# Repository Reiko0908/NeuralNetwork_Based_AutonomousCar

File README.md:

# NeuralNetwork_Based_AutonomousCar

## Project Overview
This project focuses on developing an autonomous car system powered by neural networks (NN). Inspired by the design architecture of micromouse, the car is designed to navigate autonomously using deep learning techniques. The project leverages deep learning and neural network models to enable the autonomous functionalities of the car. The neural network processes real-world sensor data to make real-time decisions for the car's navigation. The project timeline is divided into several stages:
1. **Concept Development**: Initial phase where the concept was developed.
2. **Gamepad PCB Design**: Creation of the gamepad hardware to control the car.
3. **Autonomous Car Design**: Currently in progress, focusing on the car's hardware and software integration.
4. **Neural Network Training**: Future phase where the model will be trained.
5. **Documentation**: Final phase to document the project.

## Software Architecture
- **Data Collection**: Using the gamepad (now replaced by computer control) to navigate the car in a physical map with walls. The sensors collect data and transmit it to the ESP32-S3 on the computer.
- **Machine Learning Training**: Utilizing Python and TensorFlow to train the neural network model.
- **Deployment**: Importing the trained model configurations to the car for autonomous navigation.

## Hardware

### Car Hardware
- **ESP32-S3 Super Mini**: Main microcontroller used in the car.
- **GY87 9-DOF IMU**: Inertial measurement unit for orientation and motion sensing.
- **5 VL53L0X Sensors**: Distance measurement sensors for mapping the environment.
- **L293DD Motor Driver**: Controls the motors of the car.
- **GA12 N20 Motor**: Motor with a step-up gearbox of 56:16 for movement.
- **2S Lipo Battery**

### Gamepad Hardware
- **Joysticks**
- **MPU6050 6-DOF IMU**
- **ESP32-S3 N16R8**
- **ST7789 LCD TFT SPI Screen**
- **IP5306 for Power Management**
- **Low Profile Switches**
- **Single-cell 18650 Battery**
- **Additional Buttons and Pin Headers**

## Machine Learning Training Procedure
1. **Collecting Data**: Create a physical map with walls and use the gamepad (now our computer) to control the car. The 5 VL53L0X sensors onboard will collect map data, transmit them to the ESP on the computer.
2. **Training the Model**: Use Python with TensorFlow library to train the neural network model.
3. **Deployment**: Import the trained model configurations to the car and let it navigate autonomously.

### Milestone Pictures
- **Micromouse Design Inspiration**

- **Gamepad PCB**

## Additional Information
The gamepad PCB encountered a hardware issue that cannot be fixed in time. As a workaround, we will use an external ESP32-S3 connected to the computer to control the car via BLE. We will continue to develop and improve the project.

---

*Author: pacman314159*

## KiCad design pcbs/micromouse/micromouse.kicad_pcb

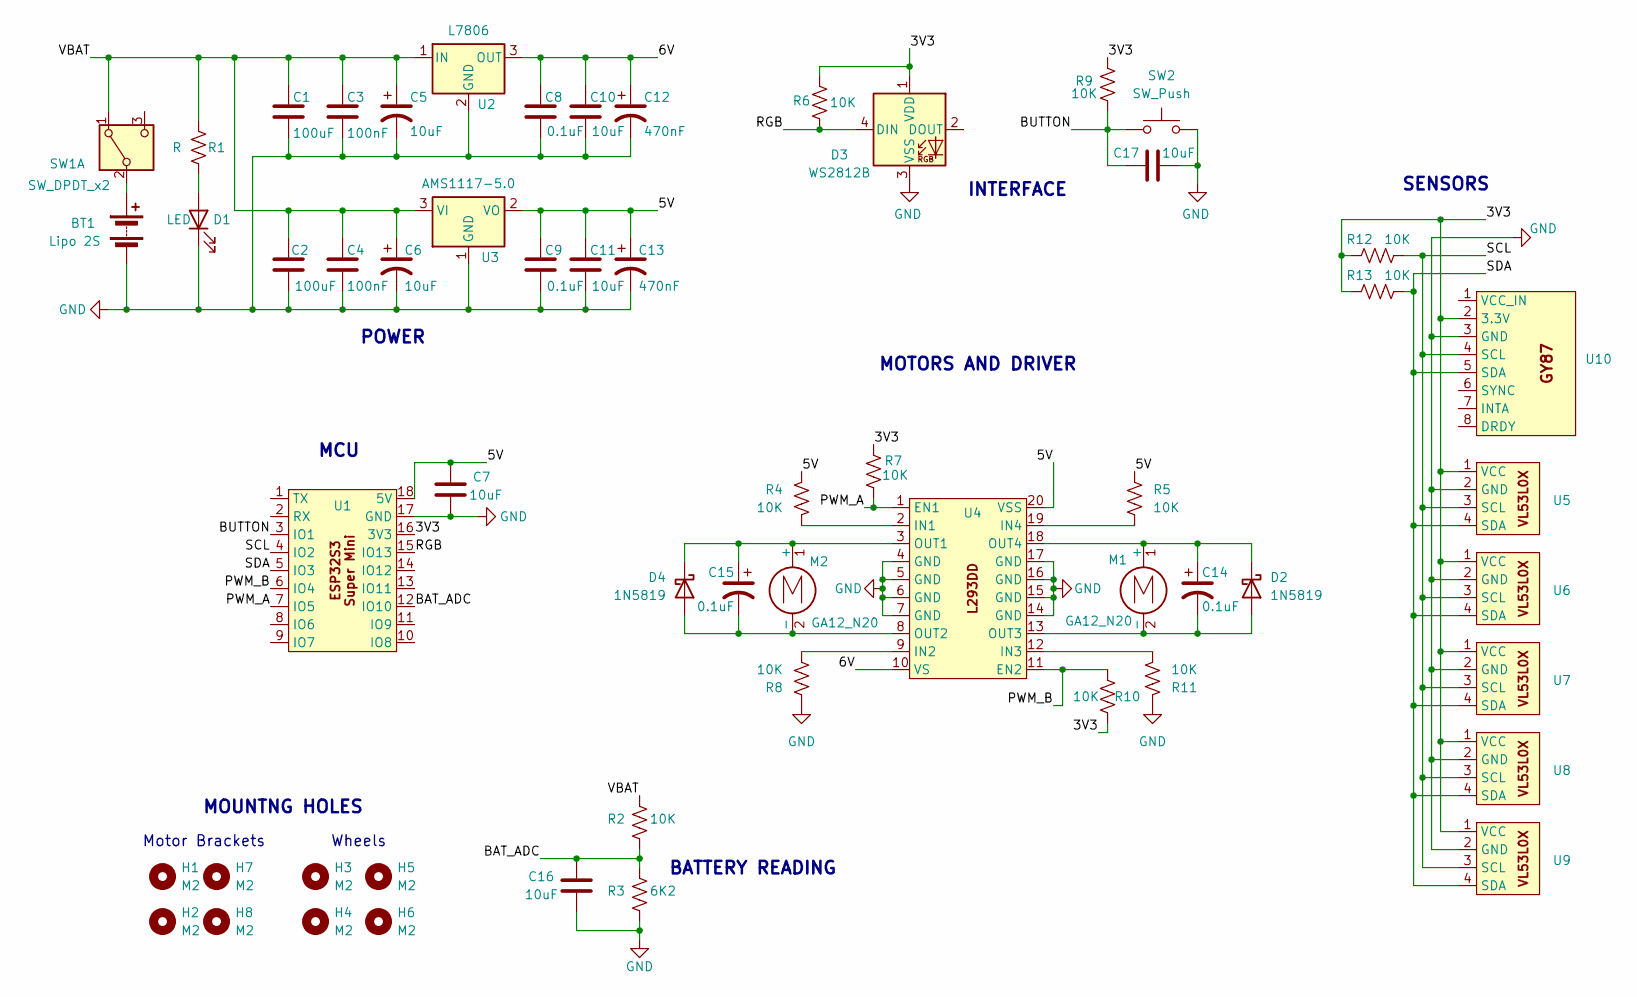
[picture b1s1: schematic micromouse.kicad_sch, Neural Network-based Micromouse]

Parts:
BT1: Lipo 2S; 2P_male
C1, C2: 100uF; C_0805_2012Metric_Pad1.18x1.45mm_HandSolder
C3, C4: 100nF; C_0805_2012Metric_Pad1.18x1.45mm_HandSolder
C5, C6: 10uF; CP_Radial_D5.0mm_P2.00mm
C7, C10, C11, C16, C17: 10uF; C_0805_2012Metric_Pad1.18x1.45mm_HandSolder
C8, C9: 0.1uF; C_0805_2012Metric_Pad1.18x1.45mm_HandSolder
C12, C13: 470nF; CP_Radial_D5.0mm_P2.00mm
C14, C15: 0.1uF; CP_Radial_D5.0mm_P2.00mm
D1: LED; LED_0805_2012Metric_Pad1.15x1.40mm_HandSolder
D2, D4: 1N5819; D_SOD-323F
D3: WS2812B; LED_WS2812B_PLCC4_5.0x5.0mm_P3.2mm
H1, H2, H3, H4, H5, H6, H7, H8: M2; MountingHole_2.2mm_M2
M1, M2: GA12_N20; 2P_male
R1: R; R_0805_2012Metric_Pad1.20x1.40mm_HandSolder
R2, R4, R5, R6, R7, R8, R9, R10, R11, R12, R13: 10K; R_0805_2012Metric_Pad1.20x1.40mm_HandSolder
R3: 6K2; R_0805_2012Metric_Pad1.20x1.40mm_HandSolder
SW1: SW_DPDT_x2; SW_SS12D07VG4
SW2: SW_Push; SW_SPST_CK_RS282G05A3
U1: esp32s3_super_mini
U2: L7806; TO-220-3_Vertical
U3: AMS1117-5.0; SOT-223-3_TabPin2
U4: SOP-20_7.5x12.8mm_P1.27mm
U5, U6, U7, U8, U9: VL53L0X_vertical
U10: GY87

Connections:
/3V3: D3.1 (VDD), R6.2, R7.2, R9.2, R10.2, R12.1, R13.1, U1.16 (3V3), U5.1 (VCC), U6.1 (VCC), U7.1 (VCC), U8.1 (VCC), U9.1 (VCC), U10.2 (3.3V)
/5V: C7.1, C9.1, C11.1, C13.1, R4.1, R5.1, U1.18 (5V), U3.2 (VO), U4.20 (VSS)
/6V: C8.1, C10.1, C12.1, U2.3 (OUT), U4.10 (VS)
/BAT_ADC: C16.1, R2.1, R3.2, U1.12 (IO10)
/BUTTON: C17.1, R9.1, SW2.1, U1.3 (IO1)
/PWM_A: R7.1, U1.7 (IO5), U4.1 (EN1)
/PWM_B: R10.1, U1.6 (IO4), U4.11 (EN2)
/RGB: D3.4 (DIN), R6.1, U1.15 (IO13)
/SCL: R12.2, U1.4 (IO2), U5.3 (SCL), U6.3 (SCL), U7.3 (SCL), U8.3 (SCL), U9.3 (SCL), U10.4 (SCL)
/SDA: R13.2, U1.5 (IO3), U5.4 (SDA), U6.4 (SDA), U7.4 (SDA), U8.4 (SDA), U9.4 (SDA), U10.5 (SDA)
/VBAT: C1.1, C2.1, C3.1, C4.1, C5.1, C6.1, R1.1, R2.2, SW1.1 (A), U2.1 (IN), U3.3 (VI)
GND: BT1.2 (-), C1.2, C2.2, C3.2, C4.2, C5.2, C6.2, C7.2, C8.2, C9.2, C10.2, C11.2, C12.2, C13.2, C16.2, C17.2, D1.1 (K), D3.3 (VSS), R3.1, R8.1, R11.1, SW2.2, U1.17 (GND), U2.2 (GND), U3.1 (GND), U4.4 (GND), U4.5 (GND), U4.6 (GND), U4.7 (GND), U4.14 (GND), U4.15 (GND), U4.16 (GND), U4.17 (GND), U5.2 (GND), U6.2 (GND), U7.2 (GND), U8.2 (GND), U9.2 (GND), U10.3 (GND)
unnamed: BT1.1 (+), SW1.2 (B)
unnamed: D1.2 (A), R1.2
unnamed: C14.2, D2.2 (A), M1.2 (-), U4.13 (OUT3)
unnamed: C14.1, D2.1 (K), M1.1 (+), U4.18 (OUT4)
unnamed: C15.2, D4.2 (A), M2.2 (-), U4.8 (OUT2)
unnamed: C15.1, D4.1 (K), M2.1 (+), U4.3 (OUT1)
unnamed: R4.2, U4.2 (IN1)
unnamed: R8.2, U4.9 (IN2)
unnamed: R11.2, U4.12 (IN3)
unnamed: R5.2, U4.19 (IN4)

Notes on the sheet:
MCU
MOUNTNG HOLES
POWER
BATTERY READING
Wheels
Motor Brackets
SENSORS
MOTORS AND DRIVER
INTERFACE

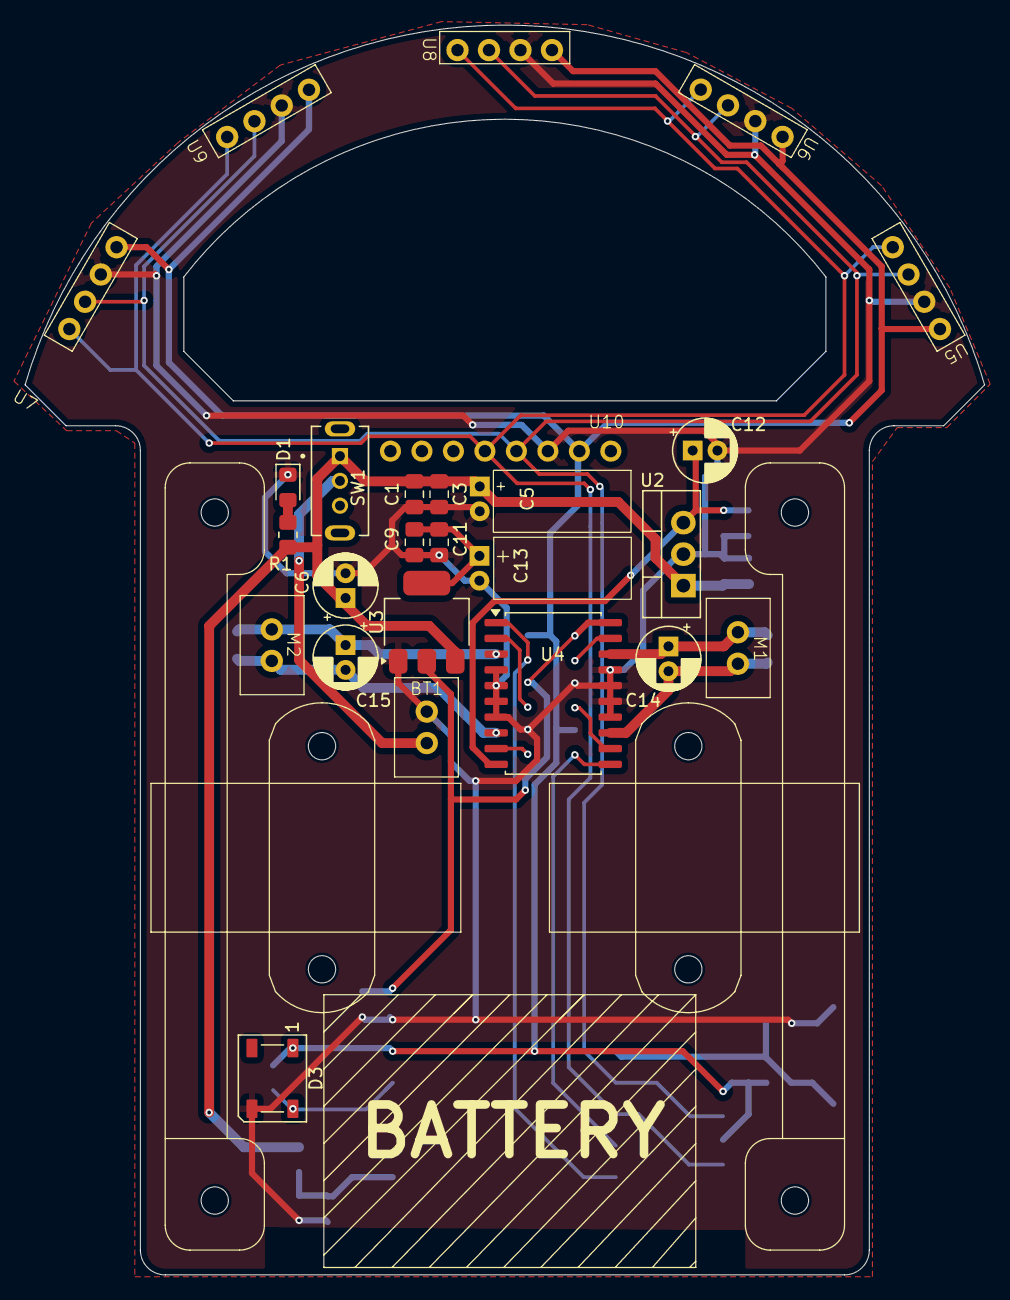
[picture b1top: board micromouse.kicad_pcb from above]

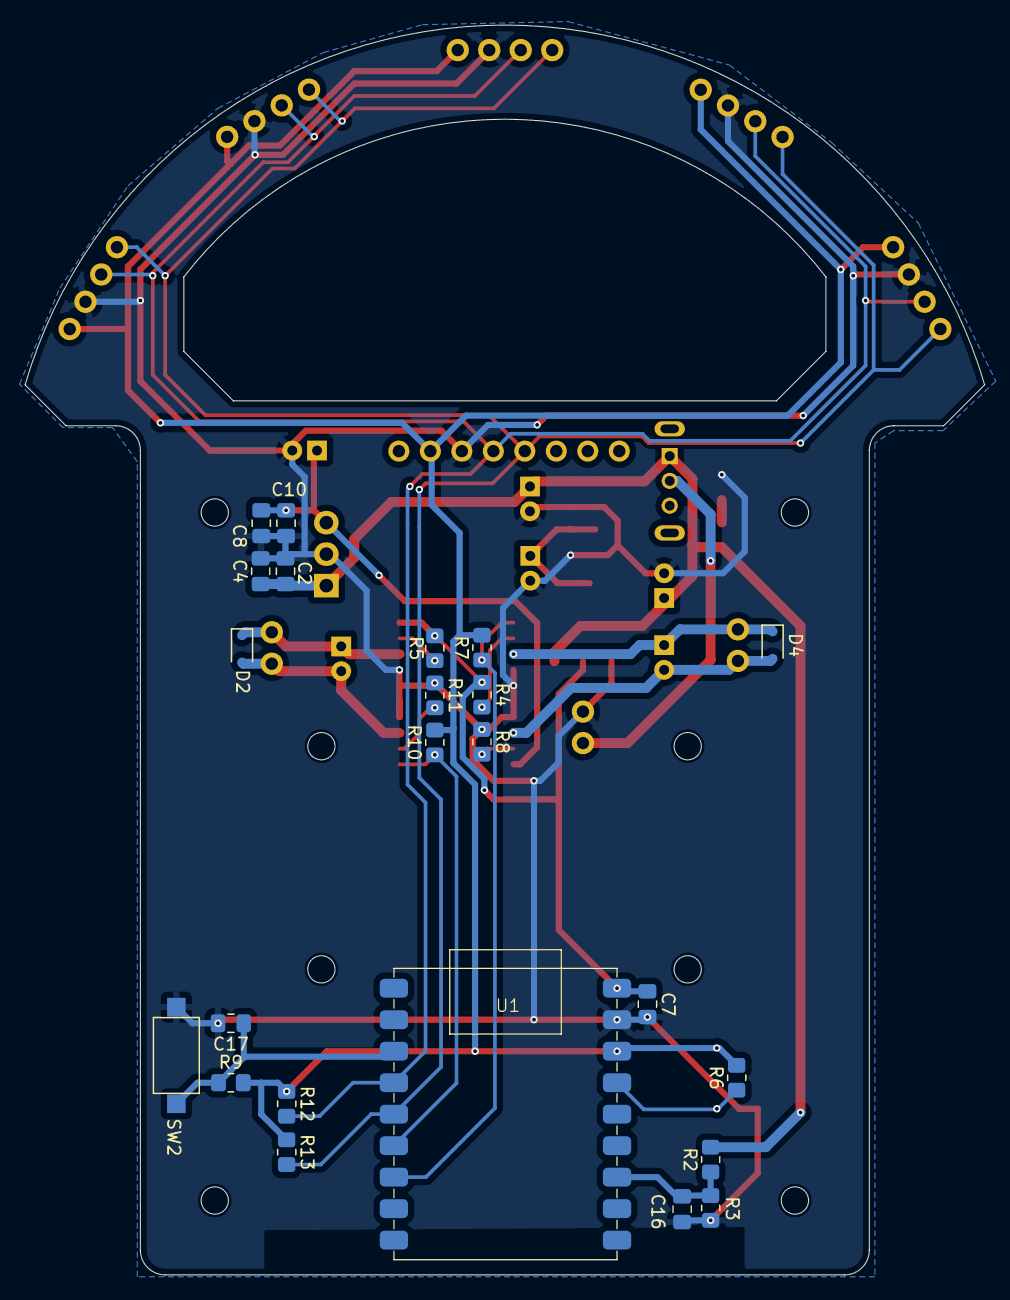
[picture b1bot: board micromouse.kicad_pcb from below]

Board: 2 copper layers, 77.4 x 100.8 mm, 57 parts (23 on the bottom side), 22 nets.

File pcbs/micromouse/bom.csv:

"Reference","Value","Datasheet","Footprint","Qty","DNP"
"BT1","Lipo 2S","~","XH_2p54:2P_male","1",""
"C1,C2","100uF","~","Capacitor_SMD:C_0805_2012Metric_Pad1.18x1.45mm_HandSolder","2",""
"C3,C4,C8,C9,C14,C15","0.1uF","~","-- mixed values --","6",""
"C5,C6,C7,C10,C11,C16,C17","10uF","~","-- mixed values --","7",""
"C12,C13","470nF","~","Capacitor_THT:CP_Radial_D5.0mm_P2.00mm","2",""
"D1","LED","~","LED_SMD:LED_0805_2012Metric_Pad1.15x1.40mm_HandSolder","1",""
"D2,D4","1N5819","http://www.vishay.com/docs/88525/1n5817.pdf","Diode_SMD:D_SOD-323F","2",""
"D3","WS2812B","https://cdn-shop.adafruit.com/datasheets/WS2812B.pdf","LED_SMD:LED_WS2812B_PLCC4_5.0x5.0mm_P3.2mm","1",""
"M1,M2","GA12_N20","~","XH_2p54:2P_male","2",""
"R1","R","~","Resistor_SMD:R_0805_2012Metric_Pad1.20x1.40mm_HandSolder","1",""
"R2,R4,R5,R6,R7,R8,R9,R10,R11,R12,R13","10K","~","Resistor_SMD:R_0805_2012Metric_Pad1.20x1.40mm_HandSolder","11",""
"R3","6K2","~","Resistor_SMD:R_0805_2012Metric_Pad1.20x1.40mm_HandSolder","1",""
"SW1","SW_DPDT_x2","~","SW_SS12D07VG4:SW_SS12D07VG4","1",""
"SW2","SW_Push","~","Button_Switch_SMD:SW_SPST_CK_RS282G05A3","1",""
"U1,U4,U5,U6,U7,U8,U9,U10","~","","-- mixed values --","8",""
"U2","L7806","http://www.st.com/content/ccc/resource/technical/document/da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","Package_TO_SOT_THT:TO-220-3_Vertical","1",""
"U3","AMS1117-5.0","http://www.advanced-monolithic.com/pdf/ds1117.pdf","Package_TO_SOT_SMD:SOT-223-3_TabPin2","1",""

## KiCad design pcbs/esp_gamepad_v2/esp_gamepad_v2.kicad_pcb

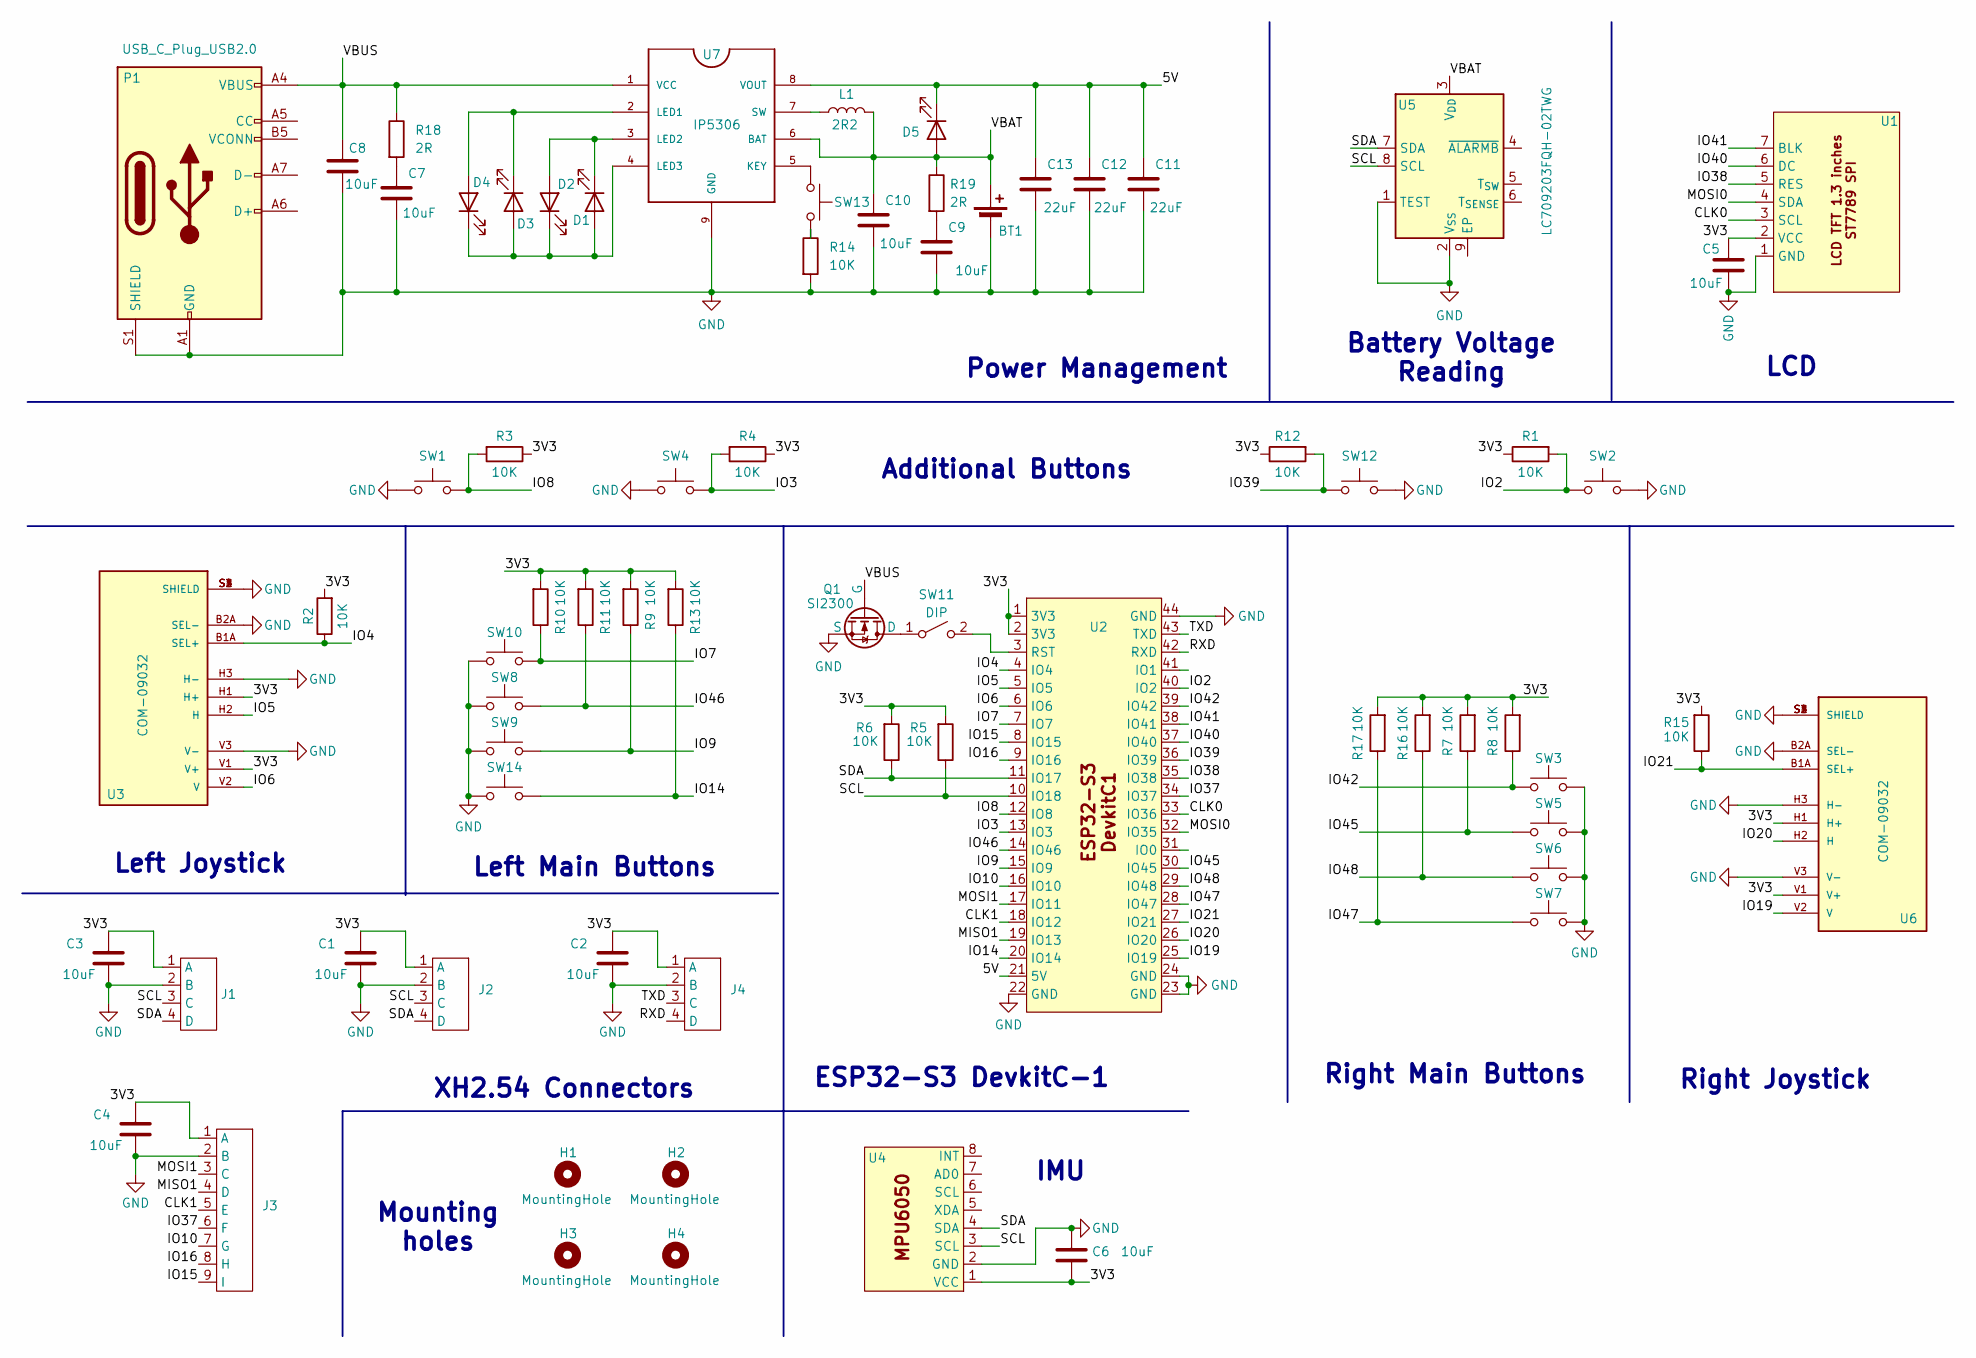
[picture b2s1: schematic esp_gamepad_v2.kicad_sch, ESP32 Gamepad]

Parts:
BT1: Battery_Cell; BatteryHolder_Keystone_1042_1x18650
C1, C2, C3, C4, C5, C6, C7, C8, C9, C10: 10uF; C_0805_2012Metric
C11, C12, C13: 22uF; CP_EIA-3528-15_AVX-H_Pad1.50x2.35mm_HandSolder
D1, D2, D3, D4, D5: LED; LED_0805_2012Metric
H1, H2, H3, H4: MountingHole; MountingHole_3.2mm_M3_Pad
J1, J2, J4: XH_2p54_4P_male
J3: XH_2p54_9P_male
L1: 2R2; L_10.4x10.4_H4.8
P1: USB_C_Plug_USB2.0; USB_C_Receptacle_GCT_USB4125-xx-x-0190_6P_TopMnt_Horizontal
Q1: SI2300; SOT-23_Handsoldering
R1, R2, R3, R4, R5, R6, R7, R8, R9, R10, R11, R12, R13, R14, R15, R16, R17: 10K; R_0805_2012Metric
R18, R19: 2R; R_0805_2012Metric
SW1, SW2: SW_Push; SW_Tactile_SPST_Angled_PTS645Vx31-2LFS
SW3, SW5, SW6, SW7, SW8, SW9, SW10, SW14: SW_Push; SW_MX_LowProfile_Kailh_Choc_V1V2_THT_Hybrid
SW4, SW12: SW_Push; SW_PUSH-12mm
SW11: DIP; SW_DIP_SPSTx01_Slide_9.78x4.72mm_W7.62mm_P2.54mm
SW13: SW_Push; SW_PUSH_6mm
U1: LCD_TFT_1.3_inches_ST7789
U2: ESP32_S3_DevkitC1
U3, U6: COM-09032; PS4_joystick; PARTREV N/A
U4: MPU6050
U5: LC709203FQH-02TWG; WDFN-8-1EP_4x3mm_P0.65mm_EP2.4x1.8mm_ThermalVias
U7: IP5306; SOIC-8-1EP_3.9x4.9mm_P1.27mm_EP2.41x3.3mm_ThermalVias

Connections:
/3V3: C1.1, C2.1, C3.1, C4.1, C5.1, C6.2, J1.1 (A), J2.1 (A), J3.1 (A), J4.1 (A), R1.1, R2.2, R3.1, R4.1, R5.2, R6.2, R7.2, R8.2, R9.2, R10.2, R11.2, R12.1, R13.2, R15.2, R16.2, R17.2, U1.2 (VCC), U2.1 (3V3), U2.2 (3V3), U3.H1 (H+), U3.V1 (V+), U4.1 (VCC), U6.H1 (H+), U6.V1 (V+)
/5V: C11.1, C12.1, C13.1, D5.1 (K), U2.21 (5V), U7.8 (VOUT)
/CLK0: U1.3 (SCL), U2.33 (IO36)
/CLK1: J3.5 (E), U2.18 (IO12)
/IO2: R1.2, SW2.2, U2.40 (IO2)
/IO3: R4.2, SW4.2, U2.13 (IO3)
/IO4: R2.1, U2.4 (IO4), U3.B1A (SEL+)
/IO5: U2.5 (IO5), U3.H2 (H)
/IO6: U2.6 (IO6), U3.V2 (V)
/IO7: R10.1, SW10.1, U2.7 (IO7)
/IO8: R3.2, SW1.2, U2.12 (IO8)
/IO9: R9.1, SW9.1, U2.15 (IO9)
/IO10: J3.7 (G), U2.16 (IO10)
/IO14: R13.1, SW14.1, U2.20 (IO14)
/IO15: J3.9 (I), U2.8 (IO15)
/IO16: J3.8 (H), U2.9 (IO16)
/IO19: U2.25 (IO19), U6.V2 (V)
/IO20: U2.26 (IO20), U6.H2 (H)
/IO21: R15.1, U2.27 (IO21), U6.B1A (SEL+)
/IO37: J3.6 (F), U2.34 (IO37)
/IO38: U1.5 (RES), U2.35 (IO38)
/IO39: R12.2, SW12.2, U2.36 (IO39)
/IO40: U1.6 (DC), U2.37 (IO40)
/IO41: U1.7 (BLK), U2.38 (IO41)
/IO42: R8.1, SW3.1, U2.39 (IO42)
/IO45: R7.1, SW5.1, U2.30 (IO45)
/IO46: R11.1, SW8.1, U2.14 (IO46)
/IO47: R17.1, SW7.1, U2.28 (IO47)
/IO48: R16.1, SW6.1, U2.29 (IO48)
/MISO1: J3.4 (D), U2.19 (IO13)
/MOSI0: U1.4 (SDA), U2.32 (IO35)
/MOSI1: J3.3 (C), U2.17 (IO11)
/RXD: J4.4 (D), U2.42 (RXD)
/SCL: J1.3 (C), J2.3 (C), R5.1, U2.10 (IO18), U4.3 (SCL), U5.8 (SCL)
/SDA: J1.4 (D), J2.4 (D), R6.1, U2.11 (IO17), U4.4 (SDA), U5.7 (SDA)
/TXD: J4.3 (C), U2.43 (TXD)
/VBAT: BT1.1 (+), C10.1, D5.2 (A), L1.2, R19.1, U5.3 (V_{DD}), U7.6 (BAT)
/VBUS: C8.1, P1.A4 (VBUS), P1.A9 (VBUS), P1.B4 (VBUS), P1.B9 (VBUS), Q1.1 (G), R18.1, U7.1 (VCC)
GND: BT1.2 (-), C1.2, C2.2, C3.2, C4.2, C5.2, C6.1, C7.2, C8.2, C9.2, C10.2, C11.2, C12.2, C13.2, J1.2 (B), J2.2 (B), J3.2 (B), J4.2 (B), P1.A1 (GND), P1.A12 (GND), P1.B1 (GND), P1.B12 (GND), P1.S1 (SHIELD), Q1.2 (S), R14.2, SW1.1, SW2.1, SW3.2, SW4.1, SW5.2, SW6.2, SW7.2, SW8.2, SW9.2, SW10.2, SW12.1, SW14.2, U1.1 (GND), U2.22 (GND), U2.23 (GND), U2.24 (GND), U2.44 (GND), U3.B2A (SEL-), U3.H3 (H-), U3.S1 (SHIELD), U3.S2 (SHIELD), U3.S3 (SHIELD), U3.S4 (SHIELD), U3.V3 (V-), U4.2 (GND), U5.1 (TEST), U5.2 (V_{SS}), U6.B2A (SEL-), U6.H3 (H-), U6.S1 (SHIELD), U6.S2 (SHIELD), U6.S3 (SHIELD), U6.S4 (SHIELD), U6.V3 (V-), U7.9 (GND)
unnamed: C7.1, R18.2
unnamed: C9.1, R19.2
unnamed: D1.2 (A), D2.1 (K), D3.2 (A), D4.1 (K), U7.4 (LED3)
unnamed: D1.1 (K), D2.2 (A), U7.3 (LED2)
unnamed: D3.1 (K), D4.2 (A), U7.2 (LED1)
unnamed: Q1.3 (D), SW11.1 (A)
unnamed: R14.1, SW13.2
unnamed: SW11.2 (B), U2.3 (RST)
unnamed: SW13.1, U7.5 (KEY)
unnamed: L1.1, U7.7 (SW)

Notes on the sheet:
Left Main Buttons
XH2.54 Connectors
Mounting holes
Battery Voltage Reading
Power Management
IMU
Additional Buttons
ESP32-S3 DevkitC-1
Right Joystick
Left Joystick
LCD
Right Main Buttons

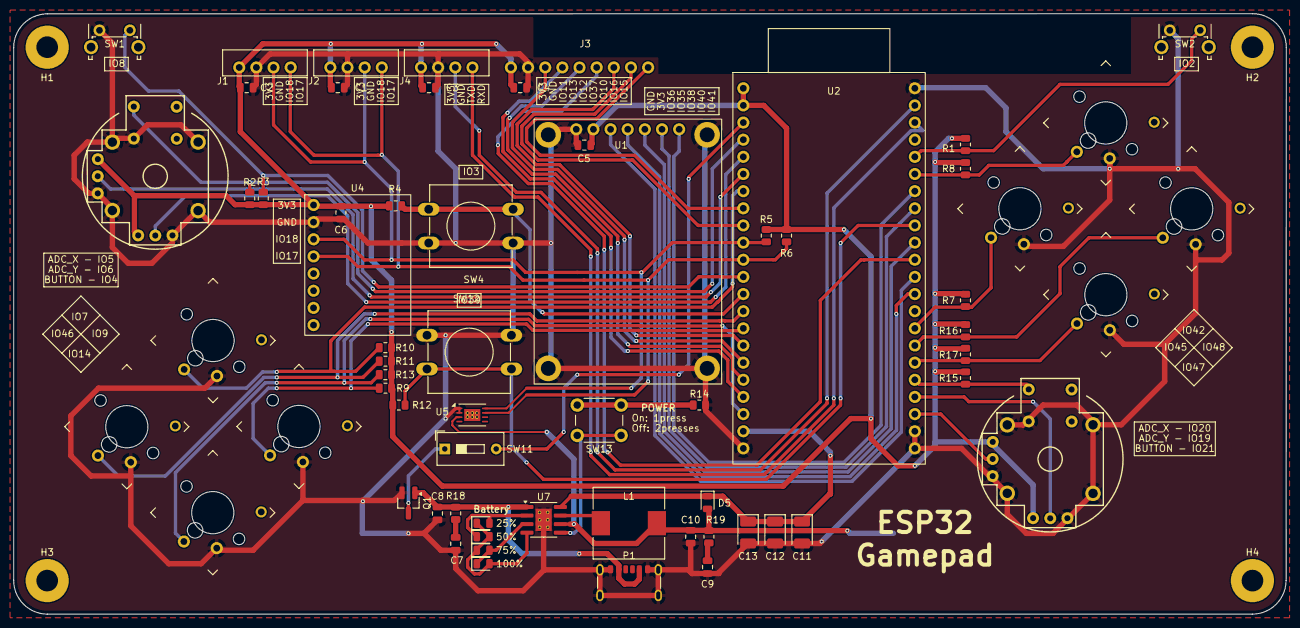
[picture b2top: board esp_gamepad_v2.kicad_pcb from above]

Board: 2 copper layers, 188.5 x 88.9 mm, 70 parts (1 on the bottom side), 49 nets.

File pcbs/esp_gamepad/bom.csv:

"Reference","Value","Datasheet","Footprint","Qty","DNP"
"BT1","Battery_Cell","~","Battery:BatteryHolder_Keystone_1042_1x18650","1",""
"C1,C2,C3,C4,C8,C9,C10,C11","10uF","~","Capacitor_SMD:C_0805_2012Metric","8",""
"C5,C6,C7","22uF","~","Capacitor_Tantalum_SMD:CP_EIA-3528-15_AVX-H_Pad1.50x2.35mm_HandSolder","3",""
"D1,D2,D3,D4,D5","LED","~","LED_SMD:LED_0805_2012Metric","5",""
"J1","2.54mm","~","Connector_PinHeader_2.54mm:PinHeader_2x10_P2.54mm_Horizontal","1",""
"L1","2R2","~","Inductor_SMD:L_10.4x10.4_H4.8","1",""
"P1","USB_C_Plug_USB2.0","https://www.usb.org/sites/default/files/documents/usb_type-c.zip","Connector_USB:USB_C_Receptacle_GCT_USB4125-xx-x_6P_TopMnt_Horizontal","1",""
"Q1","SI2301DS","https://ngspice.sourceforge.io/docs/ngspice-html-manual/manu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","Package_TO_SOT_SMD:TSOT-23","1",""
"R1,R3,R4,R5,R6,R7,R8,R9,R11,R12,R13,R14,R15,R16,R17","10K","~","Resistor_SMD:R_0805_2012Metric","15",""
"R2,R10","2R","~","Resistor_SMD:R_0805_2012Metric","2",""
"SW1,SW2,SW3,SW4,SW5,SW6,SW7,SW8,SW9,SW10,SW11,SW12,SW13","SW_Push","~","-- mixed values --","13",""
"U1,U7","COM-09032","","Joystick:Joystick","2",""
"U2","IP5306","","Package_SO:SOIC-8-1EP_3.9x4.9mm_P1.27mm_EP2.41x3.3mm_ThermalVias","1",""
"U3,U4,U6","~","","-- mixed values --","3",""
"U5","LC709203FQH-02TWG","https://www.onsemi.com/download/data-sheet/pdf/lc709203f-d.pdf","Package_DFN_QFN:WDFN-8-1EP_4x3mm_P0.65mm_EP2.4x1.8mm_ThermalVias","1",""

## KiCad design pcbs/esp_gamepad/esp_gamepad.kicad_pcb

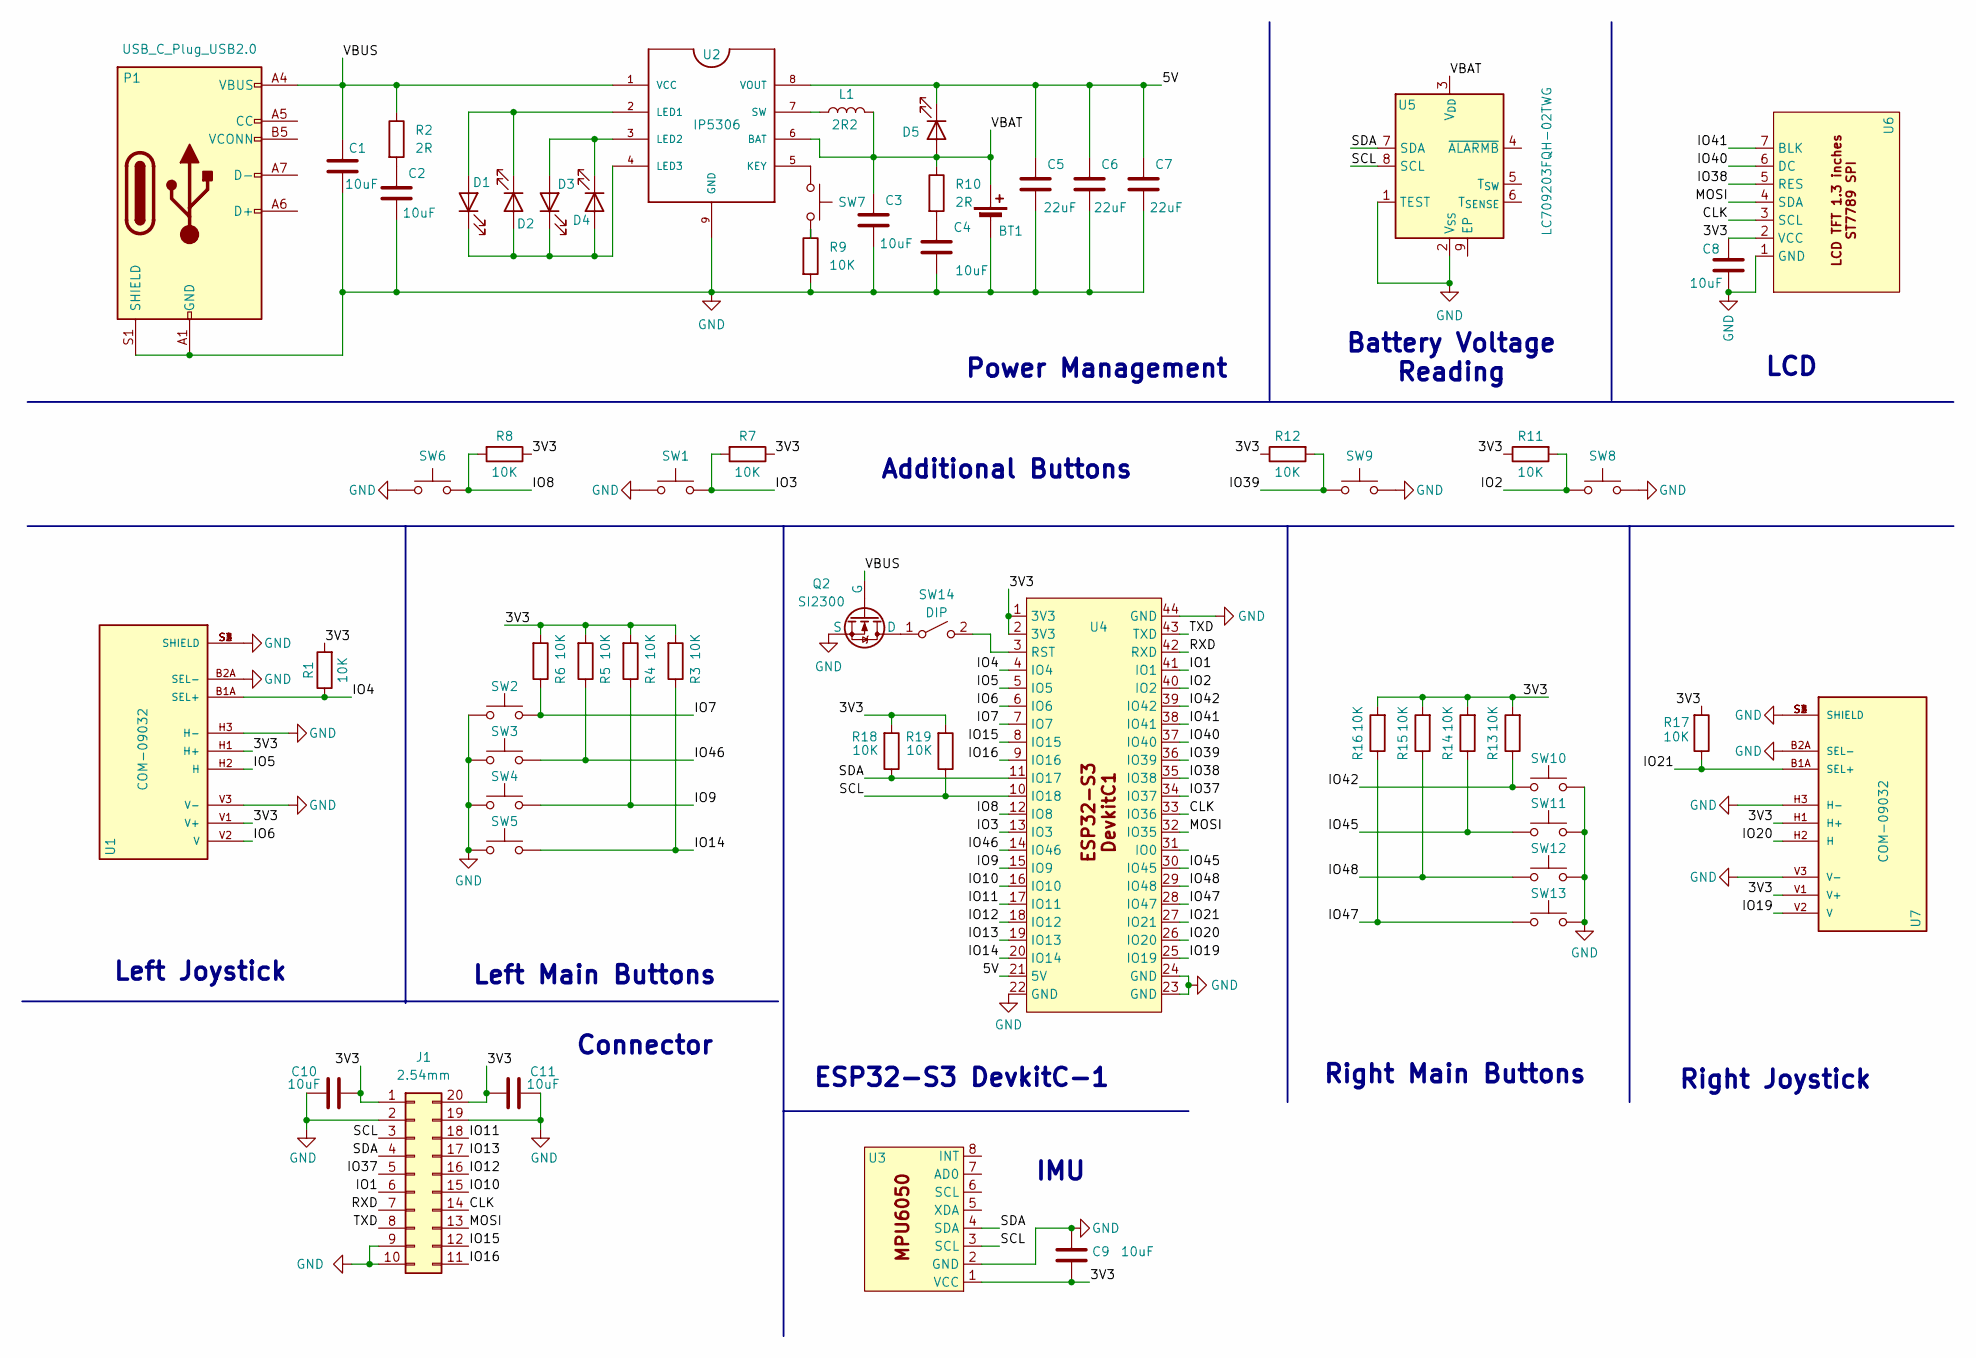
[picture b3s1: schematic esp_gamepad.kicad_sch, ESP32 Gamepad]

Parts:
BT1: Battery_Cell; BatteryHolder_Keystone_1042_1x18650
C1, C2, C3, C4, C8, C9, C10, C11: 10uF; C_0805_2012Metric
C5, C6, C7: 22uF; CP_EIA-3528-15_AVX-H_Pad1.50x2.35mm_HandSolder
D1, D2, D3, D4, D5: LED; LED_0805_2012Metric
J1: 2.54mm; PinHeader_2x10_P2.54mm_Horizontal
L1: 2R2; L_10.4x10.4_H4.8
P1: USB_C_Plug_USB2.0; USB_Type_C_6P
Q2: SI2300; SOT-23_Handsoldering
R1, R3, R4, R5, R6, R7, R8, R9, R11, R12, R13, R14, R15, R16, R17, R18, R19: 10K; R_0805_2012Metric
R2, R10: 2R; R_0805_2012Metric
SW1, SW9: SW_Push; SW_PUSH-12mm
SW2, SW3, SW4, SW5, SW10, SW11, SW12, SW13: SW_Push; SW_MX_LowProfile_Kailh_Choc_V1V2_THT_Hybrid
SW6, SW8: SW_Push; SW_Tactile_SPST_Angled_PTS645Vx31-2LFS
SW7: SW_Push; SW_PUSH_6mm
SW14: DIP; SW_DIP_SPSTx01_Slide_9.78x4.72mm_W7.62mm_P2.54mm
U1, U7: COM-09032; PS4_joystick; PARTREV N/A
U2: IP5306; SOIC-8-1EP_3.9x4.9mm_P1.27mm_EP2.41x3.3mm_ThermalVias
U3: MPU6050
U4: ESP32_S3_DevkitC1
U5: LC709203FQH-02TWG; WDFN-8-1EP_4x3mm_P0.65mm_EP2.4x1.8mm_ThermalVias
U6: LCD_TFT_1.3_inches_ST7789

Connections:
/3V3: C8.1, C9.2, C10.1, C11.1, J1.1, J1.20, R1.2, R3.2, R4.2, R5.2, R6.2, R7.1, R8.1, R11.1, R12.1, R13.2, R14.2, R15.2, R16.2, R17.2, R18.2, R19.2, U1.H1 (H+), U1.V1 (V+), U3.1 (VCC), U4.1 (3V3), U4.2 (3V3), U6.2 (VCC), U7.H1 (H+), U7.V1 (V+)
/5V: C5.1, C6.1, C7.1, D5.1 (K), U2.8 (VOUT), U4.21 (5V)
/CLK: J1.14, U4.33 (IO36), U6.3 (SCL)
/IO1: J1.6, U4.41 (IO1)
/IO2: R11.2, SW8.2, U4.40 (IO2)
/IO3: R7.2, SW1.2, U4.13 (IO3)
/IO4: R1.1, U1.B1A (SEL+), U4.4 (IO4)
/IO5: U1.H2 (H), U4.5 (IO5)
/IO6: U1.V2 (V), U4.6 (IO6)
/IO7: R6.1, SW2.1, U4.7 (IO7)
/IO8: R8.2, SW6.2, U4.12 (IO8)
/IO9: R4.1, SW4.1, U4.15 (IO9)
/IO10: J1.15, U4.16 (IO10)
/IO11: J1.18, U4.17 (IO11)
/IO12: J1.16, U4.18 (IO12)
/IO13: J1.17, U4.19 (IO13)
/IO14: R3.1, SW5.1, U4.20 (IO14)
/IO15: J1.12, U4.8 (IO15)
/IO16: J1.11, U4.9 (IO16)
/IO19: U4.25 (IO19), U7.V2 (V)
/IO20: U4.26 (IO20), U7.H2 (H)
/IO21: R17.1, U4.27 (IO21), U7.B1A (SEL+)
/IO37: J1.5, U4.34 (IO37)
/IO38: U4.35 (IO38), U6.5 (RES)
/IO39: R12.2, SW9.2, U4.36 (IO39)
/IO40: U4.37 (IO40), U6.6 (DC)
/IO41: U4.38 (IO41), U6.7 (BLK)
/IO42: R13.1, SW10.1, U4.39 (IO42)
/IO45: R14.1, SW11.1, U4.30 (IO45)
/IO46: R5.1, SW3.1, U4.14 (IO46)
/IO47: R16.1, SW13.1, U4.28 (IO47)
/IO48: R15.1, SW12.1, U4.29 (IO48)
/MOSI: J1.13, U4.32 (IO35), U6.4 (SDA)
/RXD: J1.7, U4.42 (RXD)
/SCL: J1.3, R19.1, U3.3 (SCL), U4.10 (IO18), U5.8 (SCL)
/SDA: J1.4, R18.1, U3.4 (SDA), U4.11 (IO17), U5.7 (SDA)
/TXD: J1.8, U4.43 (TXD)
/VBAT: BT1.1 (+), C3.1, D5.2 (A), L1.2, R10.1, U2.6 (BAT), U5.3 (V_{DD})
/VBUS: C1.1, P1.A4 (VBUS), P1.A9 (VBUS), P1.B4 (VBUS), P1.B9 (VBUS), Q2.2 (G), R2.1, U2.1 (VCC)
GND: BT1.2 (-), C1.2, C2.2, C3.2, C4.2, C5.2, C6.2, C7.2, C8.2, C9.1, C10.2, C11.2, J1.2, J1.9, J1.10, J1.19, P1.A1 (GND), P1.A12 (GND), P1.B1 (GND), P1.B12 (GND), P1.S1 (SHIELD), Q2.3 (S), R9.2, SW1.1, SW2.2, SW3.2, SW4.2, SW5.2, SW6.1, SW8.1, SW9.1, SW10.2, SW11.2, SW12.2, SW13.2, U1.B2A (SEL-), U1.H3 (H-), U1.S1 (SHIELD), U1.S2 (SHIELD), U1.S3 (SHIELD), U1.S4 (SHIELD), U1.V3 (V-), U2.9 (GND), U3.2 (GND), U4.22 (GND), U4.23 (GND), U4.24 (GND), U4.44 (GND), U5.1 (TEST), U5.2 (V_{SS}), U6.1 (GND), U7.B2A (SEL-), U7.H3 (H-), U7.S1 (SHIELD), U7.S2 (SHIELD), U7.S3 (SHIELD), U7.S4 (SHIELD), U7.V3 (V-)
unnamed: C2.1, R2.2
unnamed: C4.1, R10.2
unnamed: D1.2 (A), D2.1 (K), U2.2 (LED1)
unnamed: D1.1 (K), D2.2 (A), D3.1 (K), D4.2 (A), U2.4 (LED3)
unnamed: D3.2 (A), D4.1 (K), U2.3 (LED2)
unnamed: Q2.1 (D), SW14.1 (A)
unnamed: R9.1, SW7.2
unnamed: SW14.2 (B), U4.3 (RST)
unnamed: SW7.1, U2.5 (KEY)
unnamed: L1.1, U2.7 (SW)

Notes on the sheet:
Left Main Buttons
Connector
Battery Voltage Reading
Power Management
IMU
Additional Buttons
ESP32-S3 DevkitC-1
Right Joystick
Left Joystick
LCD
Right Main Buttons

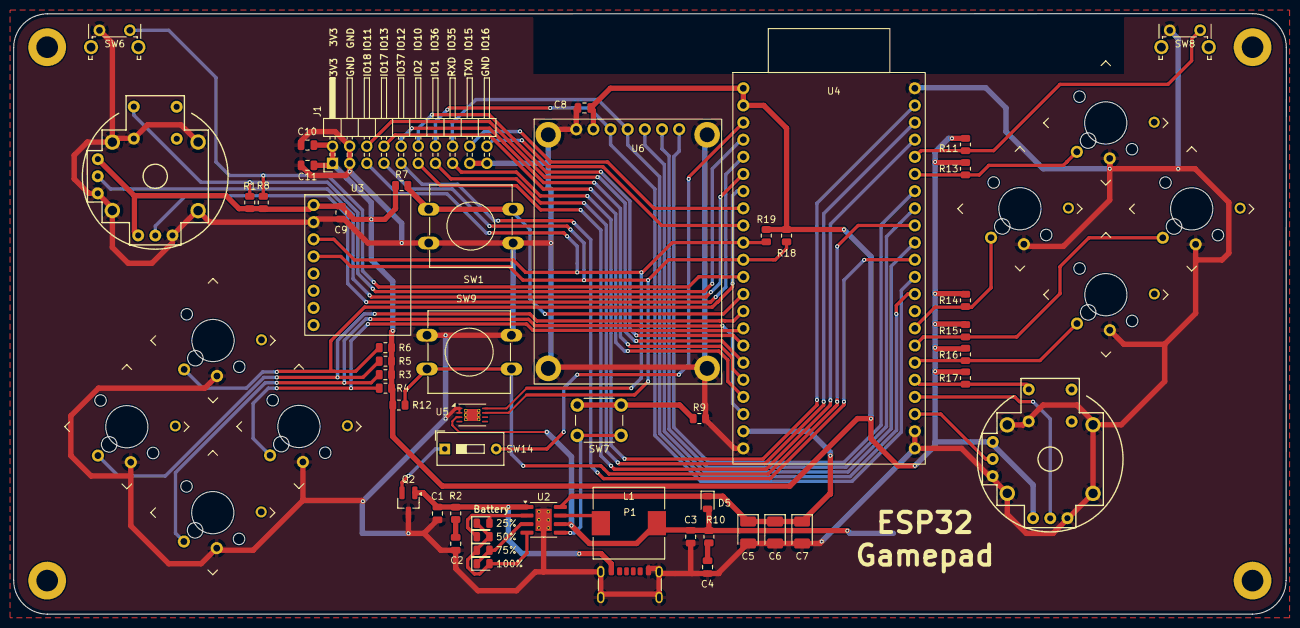
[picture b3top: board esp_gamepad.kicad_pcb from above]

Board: 2 copper layers, 188.5 x 88.9 mm, 61 parts (1 on the bottom side), 50 nets.

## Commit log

2025-01-04 [first commit ever]
2025-01-04 file structure modifications
2025-01-04 second file structure modification
2025-01-04 pwm done
2025-01-04 adc and led rgb done
2025-01-04 [Add] file system and some functions
2025-01-06 mpu6050 done
2025-01-07 esp gamepad pcb done
2025-01-07 minor edits
2025-01-09 gamepad done
2025-01-10 3d model
2025-01-12 pcb modification
2025-01-13 partition flash done
2025-01-14 tof sensor 50percent
2025-01-17 Aruino_ESP32S3_I2C_COMMUNICATION
2025-01-17 downgrade i2c version mpu6050
2025-01-17 vl53l0x i2c interface partially done
2025-01-18 mpu6050 partition api 90% done
2025-01-18 [Local save]
2025-01-20 mpu6050 partition api fixed
2025-01-23 gamepad v2 done
2025-02-09 pcb foorprint bug fixing
2025-02-28 micromouse_first_commit
2025-02-28 add motors and driver
2025-03-01 schematic_done
2025-03-04 100% done
2025-03-07 pcb gerbers done
2025-03-12 3d model and pcb micromouse done
2025-03-12 remove unnecessary files
2025-03-12 modify README
2025-03-18 [Initialize] uart_communication,neural_network dev-modules
2025-04-08 main controller creation
2025-04-08 main_controller dev
2025-04-08 mutex i2c protection
